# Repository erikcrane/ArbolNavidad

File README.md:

# ArbolNavidad
PCB de entrnamiento a la soldadura SMD

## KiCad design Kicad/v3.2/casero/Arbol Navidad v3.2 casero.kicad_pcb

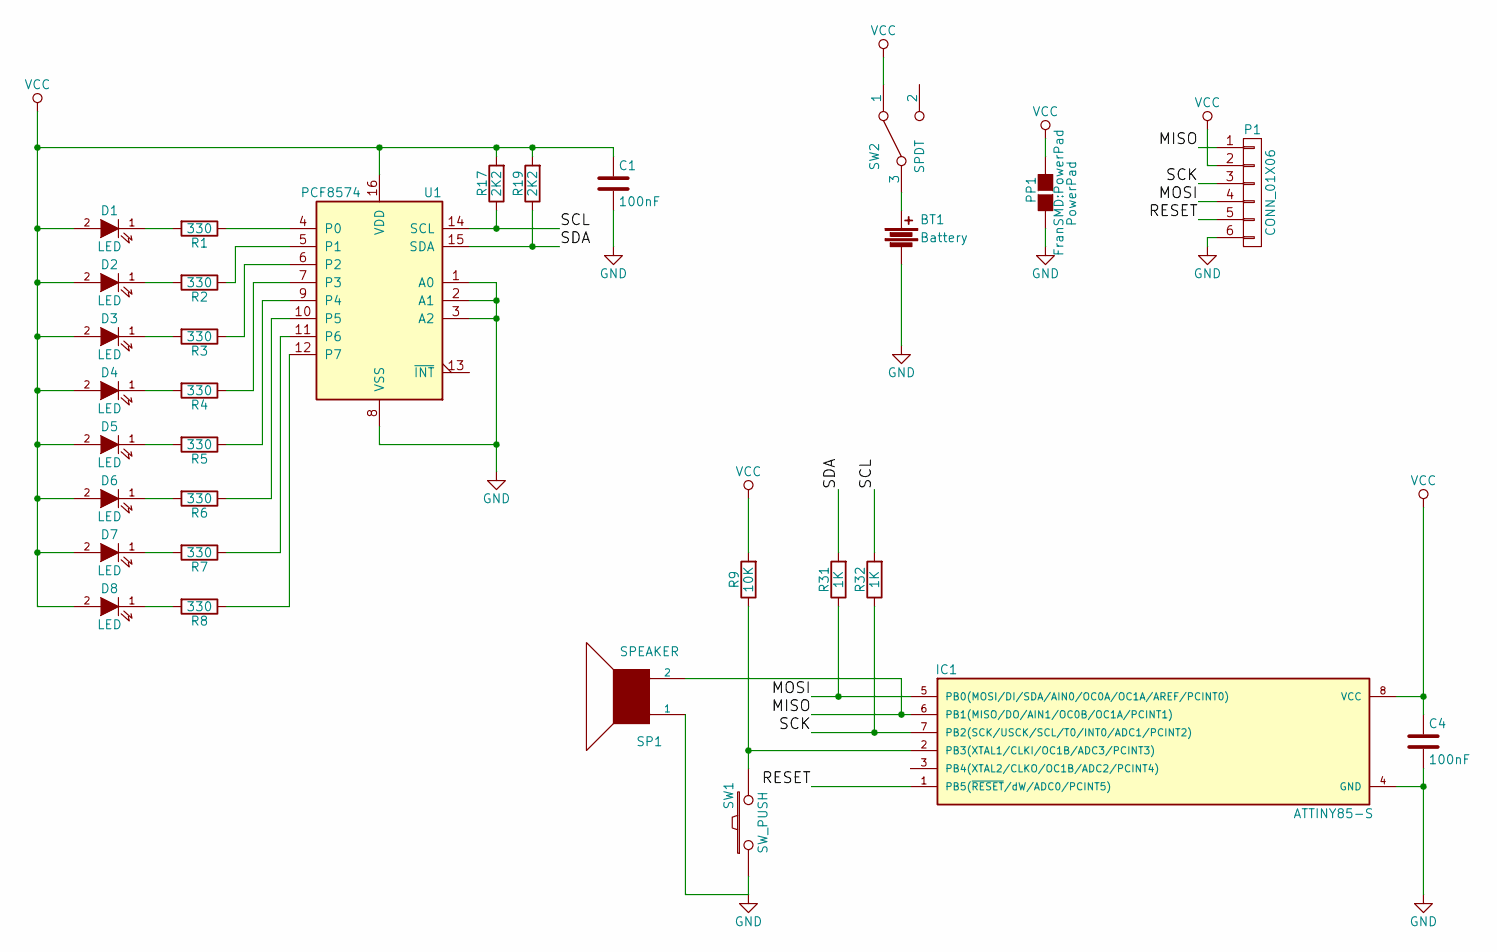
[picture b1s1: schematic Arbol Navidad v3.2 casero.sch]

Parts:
BT1: Battery; Keystone_3009_1x2450-CoinCell
C1, C4: 100nF; CAPC1206
D1, D2, D3, D4, D5, D6, D7, D8: LED; KPT-3216EC-1206
IC1: ATTINY85-S; SOIC-8_0.208i_Pitch1.27mm
P1: CONN_01X06; Pin_Header_Straight_2x03_Pitch2.54mm
PP1: PowerPad
R1, R2, R3, R4, R5, R6, R7, R8: 330; RES1206
R9: 10K; RES1206
R17, R19: 2K2; RES1206
R31, R32: 1K; RES1206
SP1: SPEAKER; Buzzer_12x8RM7.6
SW1: SW_PUSH; SW_TACTIL_SMD
SW2: SPDT; SSSS213000_SPDT
U1: PCF8574; SOIC16_7.5mm_Pitch1.27mm

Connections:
/MISO: IC1.6 (PB1(MISO/DO/AIN1/OC0B/OC1A/PCINT1)), P1.1, SP1.2
/MOSI: IC1.5 (PB0(MOSI/DI/SDA/AIN0/OC0A/OC1A/AREF/PCI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), P1.4, R31.1
/RESET: IC1.1 (PB5(~RESET~/dW/ADC0/PCINT5)), P1.5
/SCK: IC1.7 (PB2(SCK/USCK/SCL/T0/INT0/ADC1/PCINT2)), P1.3, R32.1
/SCL: R17.1, R32.2, U1.14 (SCL)
/SDA: R19.1, R31.2, U1.15 (SDA)
GND: BT1.2, C1.2, C4.2, IC1.4 (GND), P1.6, PP1.2 (PP2), SP1.1, SW1.1, SW1.3, SW1.5, U1.1 (A0), U1.2 (A1), U1.3 (A2), U1.8 (VSS)
unnamed: BT1.1, SW2.3
unnamed: D1.1 (K), R1.2
unnamed: D2.1 (K), R2.2
unnamed: D3.1 (K), R3.2
unnamed: D4.1 (K), R4.2
unnamed: D5.1 (K), R5.2
unnamed: D6.1 (K), R6.2
unnamed: D7.1 (K), R7.2
unnamed: D8.1 (K), R8.2
unnamed: IC1.2 (PB3(XTAL1/CLKI/OC1B/ADC3/PCINT3)), R9.1, SW1.2, SW1.4
unnamed: R1.1, U1.4 (P0)
unnamed: R2.1, U1.5 (P1)
unnamed: R3.1, U1.6 (P2)
unnamed: R4.1, U1.7 (P3)
unnamed: R5.1, U1.9 (P4)
unnamed: R6.1, U1.10 (P5)
unnamed: R7.1, U1.11 (P6)
unnamed: R8.1, U1.12 (P7)
VCC: C1.1, C4.1, D1.2 (A), D2.2 (A), D3.2 (A), D4.2 (A), D5.2 (A), D6.2 (A), D7.2 (A), D8.2 (A), IC1.8 (VCC), P1.2, PP1.1 (PP1), R9.2, R17.2, R19.2, SW2.1, U1.16 (VDD)

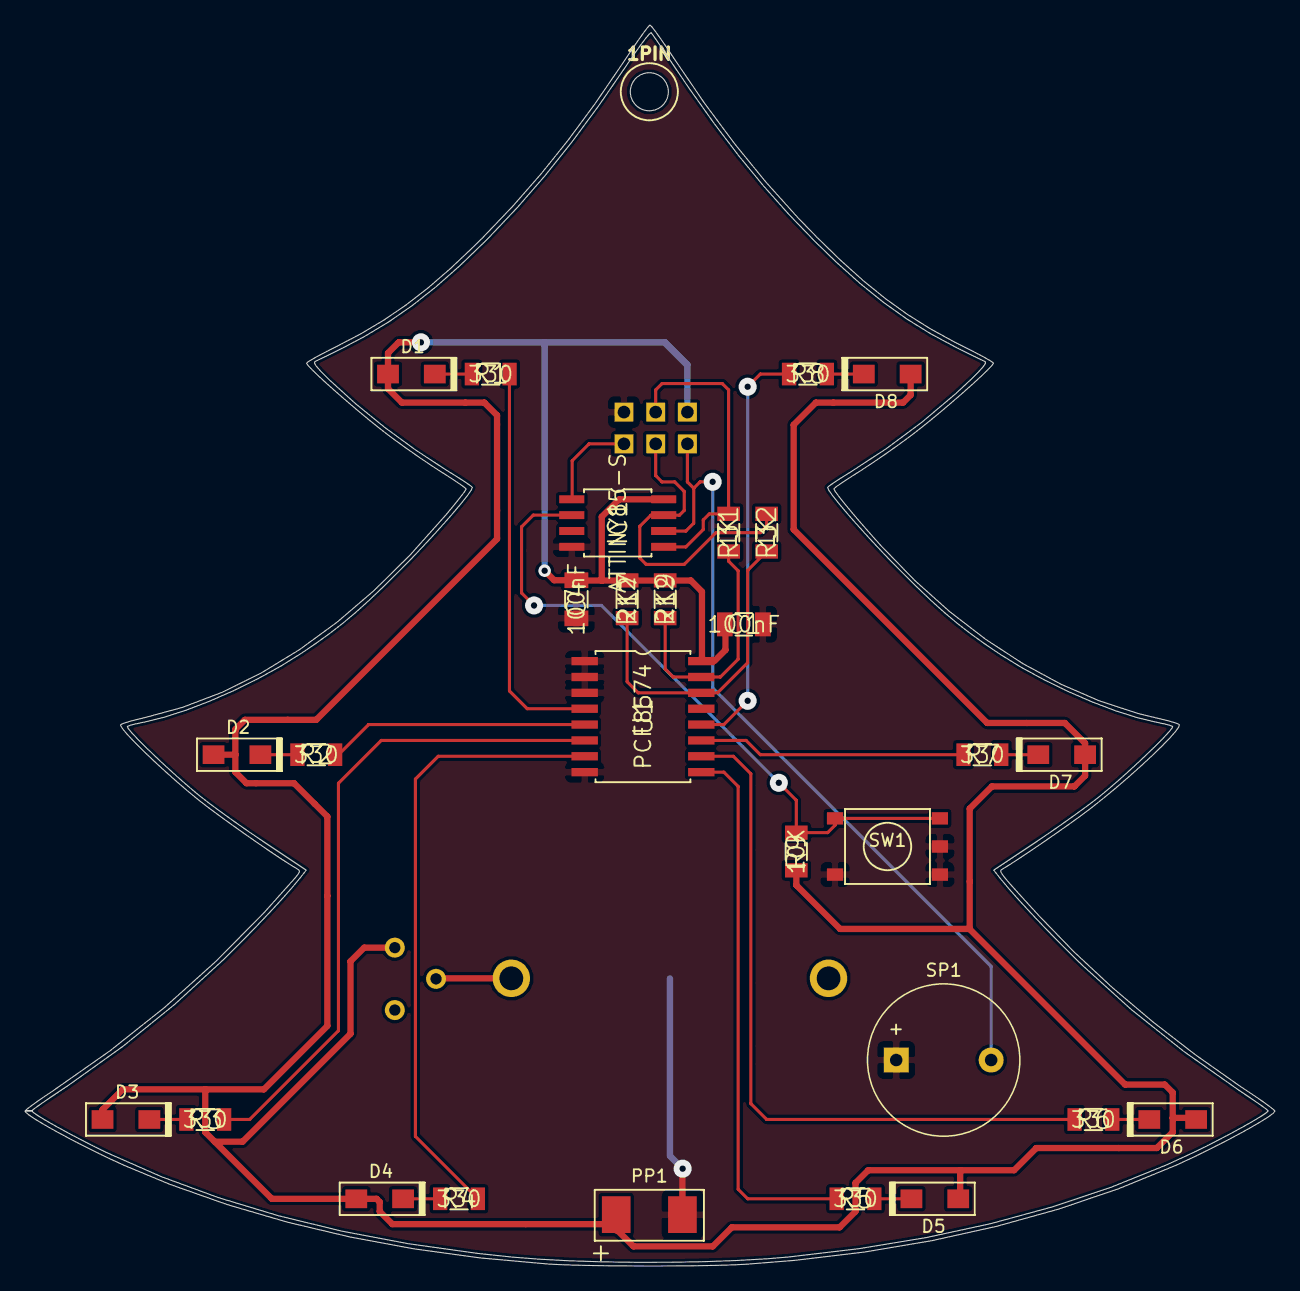
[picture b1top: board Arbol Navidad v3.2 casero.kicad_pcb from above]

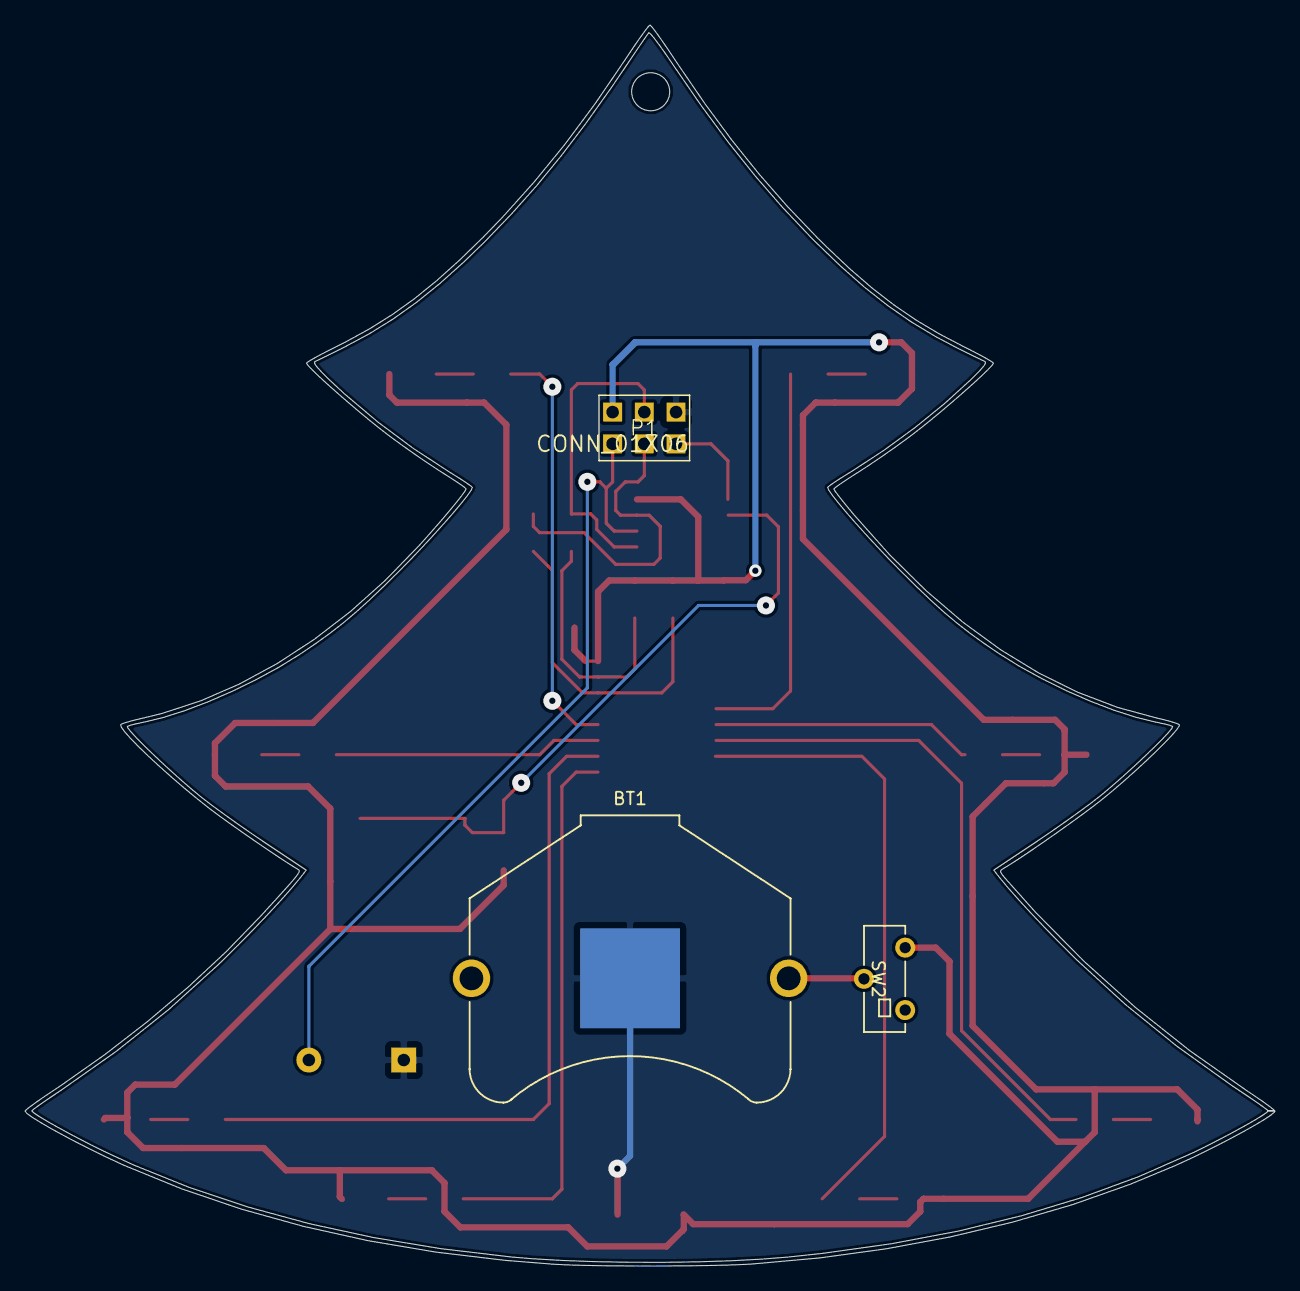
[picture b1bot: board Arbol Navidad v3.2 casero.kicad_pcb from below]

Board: 2 copper layers, 100.1 x 99.4 mm, 32 parts (3 on the bottom side), 26 nets.

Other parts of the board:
1PIN: P***; 1pin
